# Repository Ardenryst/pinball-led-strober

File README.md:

# Project description

This is a simple platform to add mods with light effects to an existing pinball machine.
The board connected to an existing lamp and once this lights up, the boards triggers its own animation. Simple as that.

Find details about hardware and firmware in their respective folders.

This project is free hardware/software, use it for your own projects if your like and let me know when you made something great!

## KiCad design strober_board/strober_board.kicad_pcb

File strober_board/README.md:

# Hardware description

The hardware is build around the `Attiny85` microcontroller (MCU), a cheap yet capable chip. To program the firmware onto the controller, an ISP (in-system programmer) is needed. You can also use something like an Arduino with the correct sketch loaded onto it.

The electronics need an external supply of 8-30V DC, reverse polarity protected local regulation is on board. The animation is triggered by an external current, the board is intended to be connected to an existing lamp and triggers as soon as this turns on. The trigger input can accept a wide voltage range of 5 to at least 24V, with no concern to polarity. For testing there is also a trigger button on the board itself that simulates an external event. Trigger input is galvanically isolated from rest of curcuit via an opto-coupler, to avoid issues with matrix switching or split power rails.

The output is connected to the board supply voltage through a current limiting resistor (R5), that has to be selected for the connected load or bridged with a jumper, if not needed. The MCU controls the output with a 12bit PWM signal, thus allowing 4096 levels of brightness with smooth fading. Output is protected against back EMF from inductive loads (e.g. EL-Wire power supply) and can supply up to 500mA of continious current.

The PCB design can either be send to a manufacturer (use the includes `Gerber-files`) or build on a commonly availible 10x23 hole proto board. Both options share the same physical board size of 30x70mm. Take a look into the interactive bill of materials `bom-folder` for what parts need to be sourced - it also greatly helps in assembly!

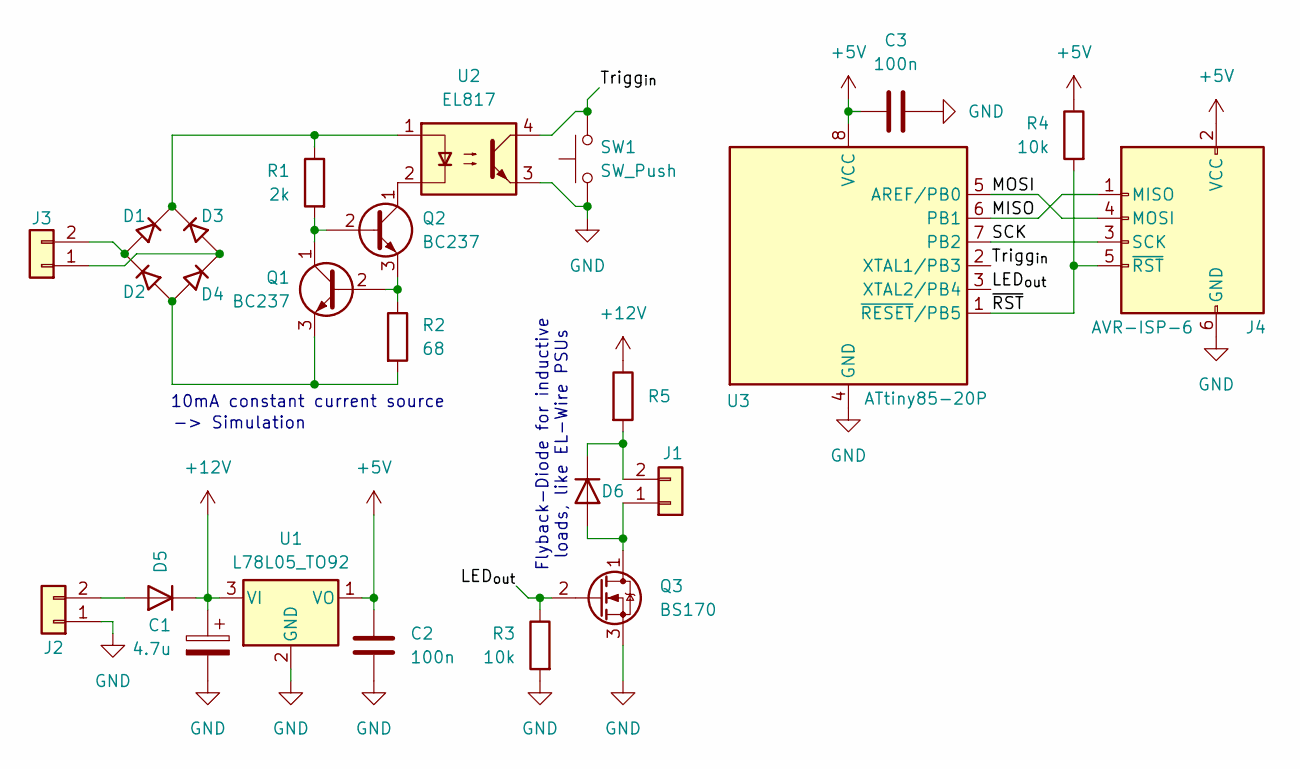
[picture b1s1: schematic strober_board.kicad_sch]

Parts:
C1: 4.7u; CP_Radial_D5.0mm_P2.50mm
C2: 100n; C_Disc_D3.0mm_W2.0mm_P2.50mm
C3: 100n; R_Axial_DIN0207_L6.3mm_D2.5mm_P10.16mm_Horizontal
D1, D2, D3, D4: D_45deg; D_A-405_P7.62mm_Horizontal
D5: D; D_DO-15_P10.16mm_Horizontal
D6: D; D_A-405_P10.16mm_Horizontal
J1: Conn_01x02; JST_EH_B2B-EH-A_1x02_P2.50mm_Vertical
J2, J3: Conn_01x02; Molex_KK-254_AE-6410-02A_1x02_P2.54mm_Vertical
J4: AVR-ISP-6; IDC-Header_2x03_P2.54mm_Vertical
Q1, Q2: BC237; TO-92_Inline_Wide
Q3: BS170; TO-92_Inline_Wide
R1: 2k; R_Axial_DIN0207_L6.3mm_D2.5mm_P10.16mm_Horizontal
R2: 68; R_Axial_DIN0207_L6.3mm_D2.5mm_P10.16mm_Horizontal
R3, R4: 10k; R_Axial_DIN0207_L6.3mm_D2.5mm_P10.16mm_Horizontal
R5: R_Axial_DIN0411_L9.9mm_D3.6mm_P5.08mm_Vertical
SW1: SW_Push; SW_PUSH_6mm
U1: L78L05_TO92; TO-92_Inline_Wide
U2: EL817; DIP-4_W7.62mm
U3: ATtiny85-20P; DIP-8_W7.62mm

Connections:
+5V: C2.2, C3.1, J4.2 (VCC), R4.1, U1.1 (VO), U3.8 (VCC)
+12V: C1.1, D5.1 (K), R5.1, U1.3 (VI)
/LED_{out}: Q3.2 (G), R3.1, U3.3 (XTAL2/PB4)
/MISO: J4.1 (MISO), U3.6 (PB1)
/MOSI: J4.4 (MOSI), U3.5 (AREF/PB0)
/SCK: J4.3 (SCK), U3.7 (PB2)
/Trigg_{in}: SW1.2, U2.4, U3.2 (XTAL1/PB3)
/~RST: J4.5 (~RST), R4.2, U3.1 (~RESET/PB5)
GND: C1.2, C2.1, C3.2, J2.1, J4.6 (GND), Q3.3 (S), R3.2, SW1.1, U1.2 (GND), U2.3, U3.4 (GND)
unnamed: D1.2 (A), D2.1 (K), J3.2
unnamed: D1.1 (K), D3.1 (K), R1.1, U2.1
unnamed: D2.2 (A), D4.2 (A), Q1.3 (E), R2.2
unnamed: D3.2 (A), D4.1 (K), J3.1
unnamed: D5.2 (A), J2.2
unnamed: D6.2 (A), J1.1, Q3.1 (D)
unnamed: D6.1 (K), J1.2, R5.2
unnamed: Q1.2 (B), Q2.3 (E), R2.1
unnamed: Q1.1 (C), Q2.2 (B), R1.2
unnamed: Q2.1 (C), U2.2

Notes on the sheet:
Flyback-Diode for inductive loads, like EL-Wire PSUs
-> Simulation
10mA constant current source

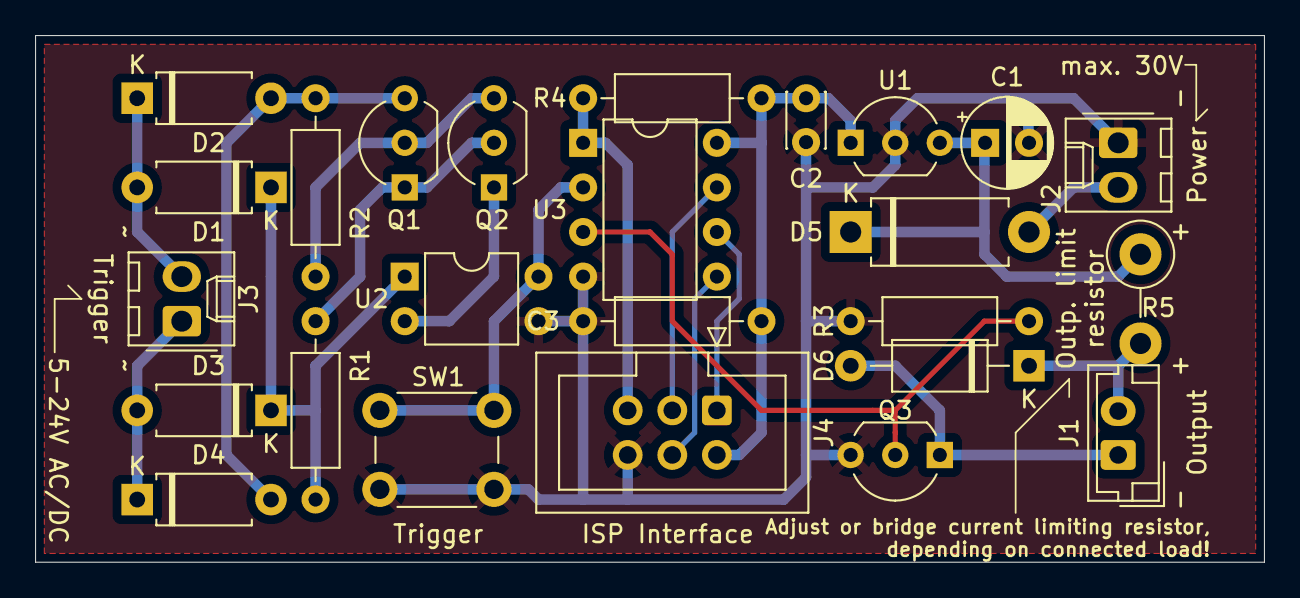
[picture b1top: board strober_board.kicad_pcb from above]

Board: 2 copper layers, 70.0 x 30.0 mm, 25 parts (0 on the bottom side), 19 nets.

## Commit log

2025-01-04 some thrown together first firmware
2025-01-04 added hardware files
2025-01-04 Create README.md
    Updated readme
2025-01-04 Production files and HW Readme
2025-01-04 3D printed case
2025-01-04 changed connectors
2025-01-04 compacted layout
2025-01-05 firmware readme
2025-01-05 added gitignore
2025-01-05 Makefile ini template
2025-02-25 add demo media
2025-03-11 minor board update
2025-03-11 Fixed reverse polarity protection
2025-03-11 burn fuses
2025-03-11 Chapter fuse in readme
2025-03-18 Readme updates
2025-03-19 remove accidentally pushed docker files
2025-04-21 improve animation
2025-04-23 fix silkscreen typo
2025-05-01 better animation
    - limit max brightness
    - better animation
    - removed commented code
2025-05-01 increase brightness variance and min brightness
